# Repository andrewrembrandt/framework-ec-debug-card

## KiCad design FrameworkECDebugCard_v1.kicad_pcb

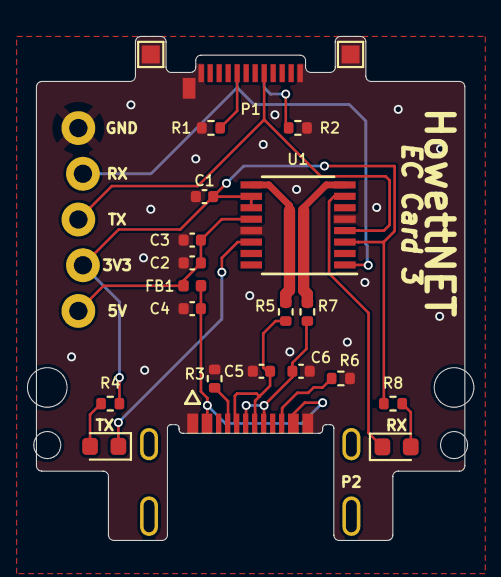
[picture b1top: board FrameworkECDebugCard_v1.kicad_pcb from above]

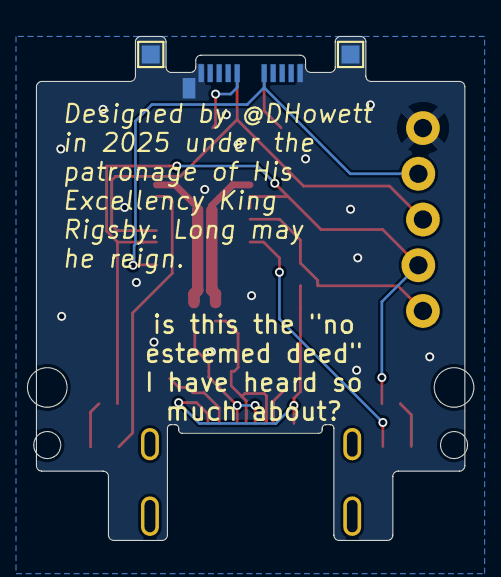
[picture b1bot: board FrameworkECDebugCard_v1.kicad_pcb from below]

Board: 2 copper layers, 23.8 x 28.0 mm, 29 parts (2 on the bottom side), 19 nets.

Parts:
C1, C3: 100nf; C_0402_1005Metric
C2: 4.7uF; C_0402_1005Metric
C4: 10nf; C_0402_1005Metric
C5, C6: 47pF; C_0402_1005Metric
D1: KT-0603R; LED_0603_1608Metric
D2: KT-0603W; LED_0603_1608Metric
FB1: 500mA; L_0402_1005Metric
H1, H3: MountingHole; MountingHole_2.2mm_M2
H2, H4: MountingHole; MountingHole_1.5mm_NPTH
J1: Conn_01x05; 1X05_LOCK
P1: 1054440011; USB_C_Plug_Molex_105444_SmallPads
P2: 2169900001; MOLEX_2169900001
R1, R2, R3, R6: 5.1k; R_0402_1005Metric
R4, R8: 270R; R_0402_1005Metric
R5, R7: 27R; R_0402_1005Metric
TP1, TP2, TP3, TP4: TestPoint; TestPoint_Pad_1.0x1.0mm
U1: FT230XS; SSOP-16_3.9x4.9mm_P0.635mm

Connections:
/DIN: J1.4, P1.B8 (DIN), U1.1 (TXD)
/DOUT: J1.3, P1.A8 (DOUT), U1.4 (RXD)
/F_USBD+: R7.2, U1.8 (USBDP)
/F_USBD-: R5.2, U1.9 (USBDM)
/RXLED: D2.1 (K), U1.7 (CBUS2)
/TXLED: D1.1 (K), U1.14 (CBUS1)
/USBD+: C6.1, P2.A6 (D+), P2.B6 (D+), R7.1
/USBD-: C5.1, P2.A7 (D-), P2.B7 (D-), R5.1
GND: C1.2, C2.2, C3.2, C4.2, C5.2, C6.2, J1.5, P1.A1 (GND), P1.A12 (GND), P1.B1 (GND), P1.B12 (GND), P1.S1 (SHIELD), P2.A1 (GND), P2.A12 (GND), R1.2, R2.2, R3.1, R6.1, TP1.1, TP2.1, TP3.1, TP4.1, U1.5 (GND), U1.13 (GND)
unnamed: C4.1, FB1.1, P2.A4 (VBUS), P2.A9 (VBUS)
unnamed: D1.2 (A), R4.2
unnamed: D2.2 (A), R8.2
unnamed: P1.A5 (CC), R1.1
unnamed: P1.A4 (VBUS), P1.A9 (VBUS), P1.B4 (VBUS), P1.B9 (VBUS)
unnamed: P1.B5 (VCONN), R2.1
unnamed: P2.A5 (CC1), R3.2
unnamed: P2.B5 (CC2), R6.2
VBUS_HOST: C2.1, C3.1, FB1.2, J1.1, U1.12 (VCC)
VCCIO: C1.1, J1.2, R4.1, R8.1, U1.3 (VCCIO), U1.10 (3V3OUT), U1.11 (~RESET)

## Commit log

2022-07-10 Add the first rev of the card:
    Uses FT230XS and 0603 components.
2022-07-10 v1.1: switch to FT230XQ (QFN) and 0402 components instead of 0603
2022-07-10 Schematic: clarify VBUS_{HOST,DEV}, reorganize to avoid flyover wires
2022-07-12 Rework board per Kieran's suggestions
    - Route the USB differential pairs together, and without vias
    - Had to move back to the SSOP package because the QFN package
    would require a crossover (yes, no, it doesn't make any sense)
    - Ground fill
    - Hand-route
    - Redistribute passives to be more reasonably laid out
2022-07-12 Add a 1x5 header to break out the EC/FTDI pins
    This header uses the SparkFun "LOCK" footprint, which should
    allow me to click in a header without soldering it down.
2022-07-12 Re-route the USB differential pairs following the DigiKey guide
    These traces are *C H O N K Y*
2022-07-14 Move the passives closer to USB, use 6mil traces to passives
2022-07-14 Re-route VCCIO to move cap closer to 3V3OUT, reroute RXLED in the new space
2022-07-14 Re-route everything to avoid B.Cu cuts across diff pair
    Switched the positions of the TX and RX LEDs to match which side of the
    chip they're on. Significantly re-routed TX/RX. Added via stitching.
    The ground planes are much more contiguous, except for U1 pad 5 which
    connects to GND on the back with a via.
    (Kieran's suggestion was to remove the lines on the back that cut
    horizontally across the differential pair; I don't know if having
2022-07-16 Add more stitching vias
2025-01-20 Update to KiCad 8, use narrower pads on USB C plug (PCBWay may mfg this)
2025-01-21 sch: update to kicad 8
2025-01-23 ec card 3: recessed mid-mount usb c receptacle, fully rerouted
2025-01-23 ec3: rebuild the pcb to the same shape as the usb c card; not routed
2025-01-25 ec3: route it! use JLCPCB's tolerances
2025-01-27 ec3: length-match the D+/- pair, move logo
2025-01-27 ec3: switch to 'real' molex footprint
2025-01-27 ec3: branding! fun! whimsy!
2025-01-27 ec3: specify LEDs, some pad types
2025-01-27 ec3: remove empty accidental footprint
2025-01-27 ec3: drc moved a bunch of things around by fractional mm
2025-01-27 ec3: geographical reannotate
2025-01-27 ec3: ground the USB C receptacle shields; no thermal spokes
2025-01-27 ec3: fix typo
2026-03-02 Remove legacy KiCad v5 files
2026-03-02 Upgrade to KiCad 9
2026-03-03 Ignore JLCPCB Fabrication Toolkit files
2026-03-03 Add JLCPCB LCSC part numbers
2026-03-03 Fabrication files export settings (PCBWay etc)
2026-03-09 Remove vias-in-pad
2026-03-09 Add PCBWay design rules
2026-03-09 Remove P1 from bom and tune Fabrication settings for PCBWay
2026-03-09 Add manual BOM
2026-03-10 Exclude P2 from PCBWay/JLCPCB assembly (cheaper to do it manually)
